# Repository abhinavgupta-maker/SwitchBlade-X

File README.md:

The firmware location is: SwitchBlade-X -> Firmware -> SwitchBlade_
# HackPad SwitchBlade-X

## Hardware Overview
- MCU: RP2040
- Matrix: 2x4 (8 Keys)
- Encoder: EC11 Rotary Encoder
- Display: 0.91" SSD1306 I2C OLED
- RGB: 9x SK6812 MINI-E Addressable LEDs

## Firmware Framework
Designed using QMK firmware architecture for:
- Layered key mapping
- Matrix scanning
- Encoder interrupt handling
- I2C OLED communication
- WS2812/SK6812 LED control

## Feature Implementation

### Matrix Scanning
2 row pins, 4 column pins, COL2ROW diode configuration.

### Encoder
Clockwise → Goes up in the keybind layer 
Counter-clockwise → Goes back in the keybind layer

### OLED
Displays:
- Animations
- Which layer you are on while switching

### RGB
Default breathing effect with configurable modes.

## Expansion Ready
Firmware supports:
- Additional layers
- RGB reactive effects
- Encoder layer control
- WPM display
## How to use it?
To use it you have to first customize your firmware according to your needs and then flash the esp and then you can use it easily
I made this project as when i am either coding or doing some robotics stuff i have problem doing some things and to make it easier i have make this hackpad so i can use it for gaming or coding with the encoder chaging the layer of keybinds to use aand the oled and rgb adding the vibe to it

Reference	Qty	Value	DNP	Exclude from BOM	Exclude from Board	Footprint	Datasheet
330ohm1	1	R				Resistor_SMD:R_0201_0603Metric	~
D1,D2,D3,D4,D5,D6,D7,D8	8	1N4148WT				Diode_SMD:D_SOD-523	https://www.diodes.com/assets/Datasheets/ds30396.pdf
D9,D10,D11,D12,D13,D14,D15,D16,D17	9	SK6812MINI-E				footprints:SK6812MINI-E_fixed	https://cdn-shop.adafruit.com/product-files/4960/4960_SK6812MINI-E_REV02_EN.pdf
J1	1	Conn_01x04_Pin				KiCad-SSD1306-0.91-OLED-4pin-128x32:SSD1306-0.91-OLED-4pin-128x32	~
SW1,SW2,SW3,SW4,SW5,SW6,SW7,SW8	8	SW_Push				Button_Switch_Keyboard:SW_Cherry_MX_1.00u_PCB	~
SW9	1	RotaryEncoder_Switch				Rotary_Encoder:RotaryEncoder_Alps_EC11E-Switch_Vertical_H20mm	~
U1	1	MOUDLE-SEEEDUINO-XIAO				footprints:XIAO-Generic-Hybrid-14P-2.54-21X17.8MM

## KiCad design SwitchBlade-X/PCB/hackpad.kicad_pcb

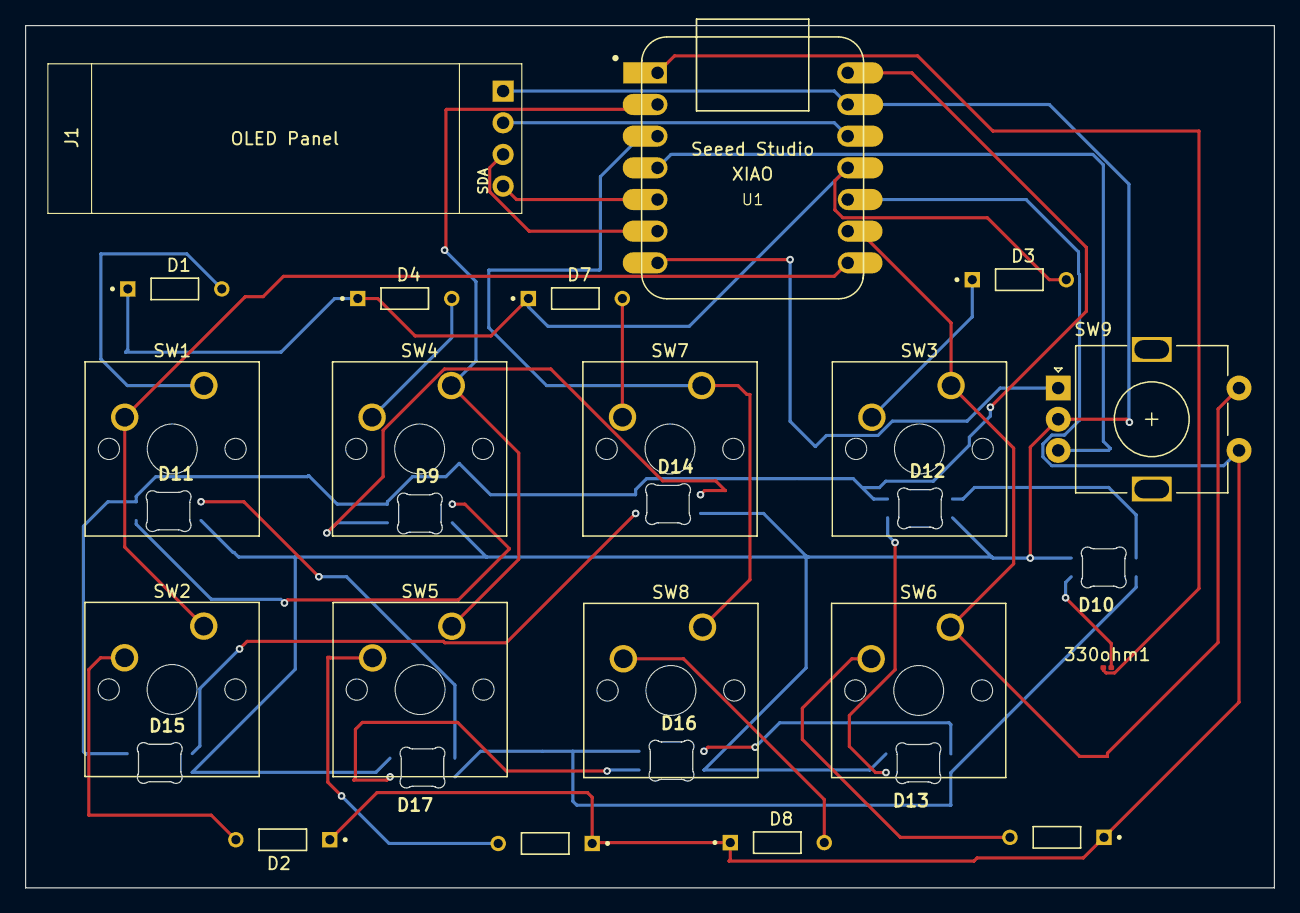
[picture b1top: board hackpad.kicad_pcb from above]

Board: 2 copper layers, 100.2 x 69.1 mm, 29 parts (0 on the bottom side), 31 nets.

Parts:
330ohm1: R; R_0201_0603Metric
D1, D2, D3, D4, D5, D6, D7, D8: 1N4148WT; DIOAD753W49L380D172B
D9, D10, D11, D12, D13, D14, D15, D16, D17: SK6812MINI-E; SK6812MINI-E_fixed
J1: Conn_01x04_Pin; SSD1306-0.91-OLED-4pin-128x32
SW1, SW2, SW3, SW4, SW5, SW6, SW7, SW8: SW_Push; SW_Cherry_MX_1.00u_PCB
SW9: RotaryEncoder_Switch; RotaryEncoder_Alps_EC11E-Switch_Vertical_H20mm
U1: MOUDLE-SEEEDUINO-XIAO; XIAO-Generic-Hybrid-14P-2.54-21X17.8MM

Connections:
+3.3V: J1.2, U1.12 (3V3)
+5V: D9.1 (VDD), D10.1 (VDD), D11.1 (VDD), D12.1 (VDD), D13.1 (VDD), D14.1 (VDD), D15.1 (VDD), D16.1 (VDD), D17.1 (VDD), U1.14 (5V)
COL1: SW1.2, SW2.1, U1.8 (PB09_A7_D7_RX)
COL2: SW4.1, SW5.1, U1.2 (PA4_A1_D1)
COL3: SW7.1, SW8.1, U1.3 (PA10_A2_D2)
COL4: SW3.1, SW6.1, SW9.S2, U1.9 (PA7_A8_D8_SCK)
DOUT: D11.4 (DIN), D17.2 (DOUT)
GND: D9.3 (VSS), D10.3 (VSS), D11.3 (VSS), D12.3 (VSS), D13.3 (VSS), D14.3 (VSS), D15.3 (VSS), D16.3 (VSS), D17.3 (VSS), J1.1, SW9.C, U1.13 (GND)
LED_PIN: 330ohm1.1, U1.1 (PA02_A0_D0)
unnamed: D1.A, SW1.1
unnamed: D2.A, SW2.2
unnamed: D3.K, SW3.2
unnamed: D4.A, SW4.2
unnamed: D5.A, SW5.2
unnamed: D6.A, SW6.2
unnamed: D7.A, SW7.2
unnamed: D8.A, SW8.2
unnamed: 330ohm1.2, D10.4 (DIN)
unnamed: D10.2 (DOUT), D12.4 (DIN)
unnamed: D9.4 (DIN), D11.2 (DOUT)
unnamed: D12.2 (DOUT), D13.4 (DIN)
unnamed: D13.2 (DOUT), D16.4 (DIN)
unnamed: D9.2 (DOUT), D14.4 (DIN)
unnamed: D14.2 (DOUT), D15.4 (DIN)
unnamed: D16.2 (DOUT), D17.4 (DIN)
Oled_SCK: J1.3, U1.6 (PA9_A5_D5_SCL)
Oled_SDA: J1.4, U1.5 (PA8_A4_D4_SDA)
ROW1: D1.K, D3.A, D4.K, D7.K, U1.11 (PA6_A10_D10_MOSI)
ROW2: D2.K, D5.K, D6.K, D8.K, SW9.S1, U1.10 (PA5_A9_D9_MISO)
d3: SW9.B, U1.4 (PA11_A3_D3)
d6: SW9.A, U1.7 (PB08_A6_D6_TX)
